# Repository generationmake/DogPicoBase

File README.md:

# DogPicoBase
Board with Electronic Assembly DOG graphic display for the Raspberry Pi Pico

## pin usage

### Raspberry Pi Pico connector CN1

| **Pin** | **Pin Name** | **Signal**    | **Description**                  |
|:-------:|:------------:|:-------------:|:--------------------------------:|
| 1       | GP0          | DIS_A0        | data/command for display         |
| 2       | GP1          | DIS_RESET     | reset for display                |
| 3       | GND          | GND           |                                  |
| 4       | GP2          |               |                                  |
| 5       | GP3          |               |                                  |
| 6       | GP4          |               |                                  |
| 7       | GP5          |               |                                  |
| 8       | GND          | GND           |                                  |
| 9       | GP6          | DIS_CLK       | clock for display on SPI0        |
| 10      | GP7          | DIS_SI        | data for display on SPI0         |
| 11      | GP8          |               |                                  |
| 12      | GP9          |               |                                  |
| 13      | GND          | GND           |                                  |
| 14      | GP10         |               |                                  |
| 15      | GP11         |               |                                  |
| 16      | GP12         | I2C0_SDA      | to connector CN3                 |
| 17      | GP13         | I2C0_SCL      | to connector CN3                 |
| 18      | GND          | GND           |                                  |
| 19      | GP14         | DIS_CS        | chip select for display          |
| 20      | GP15         |               |                                  |
| 21      | GP16         | UART0_TX      | to connector CN2                 |
| 22      | GP17         | UART0_RX      | to connector CN2                 |
| 23      | GND          | GND           |                                  |
| 24      | GP18         | I2C1_SDA      | to connector CN4                 |
| 25      | GP19         | I2C1_SCL      | to connector CN4                 |
| 26      | GP20         | DISPLAY_BL_3  | backlight channel 3              |
| 27      | GP21         | DISPLAY_BL_2  | backlight channel 2              |
| 28      | GND          | GND           |                                  |
| 29      | GP22         | DISPLAY_BL_1  | backlight channel 1              |
| 30      | RUN          | RESET         | Reset for Board                  |
| 31      | GP26         | KEYPAD_A0     | analog input for keys            |
| 32      | GP27         |               |                                  |
| 33      | GND          | GND           |                                  |
| 34      | GP28         |               |                                  |
| 35      | ADC_VREF     |               |                                  |
| 36      | 3V3 (OUT)    | 3V3-rail      | supply voltage for board         |
| 37      | 3V3_EN       |               |                                  |
| 38      | GND          | GND           |                                  |
| 39      | VSYS         |               |                                  |
| 40      | VBUS         | 5V-rail       | supply voltage for board         |

### Qwiic I2C connector CN3

compatible to Sparkfun Qwiic. JST SH 1mm 4-pin.

| **Pin** | **Signal**    | **Description**                  |
|:-------:|:-------------:|:--------------------------------:|
| 1       | GND           |                                  |
| 2       | VCC           |                                  |
| 3       | I2C0_SDA      |                                  |
| 4       | I2C0_SCL      |                                  |

### Qwiic I2C connector CN4

compatible to Sparkfun Qwiic. JST SH 1mm 4-pin.

| **Pin** | **Signal**    | **Description**                  |
|:-------:|:-------------:|:--------------------------------:|
| 1       | GND           |                                  |
| 2       | VCC           |                                  |
| 3       | I2C1_SDA      |                                  |
| 4       | I2C1_SCL      |                                  |

### serial connector CN2

JST SH 1mm 4-pin.

| **Pin** | **Signal**    | **Description**                  |
|:-------:|:-------------:|:--------------------------------:|
| 1       | GND           |                                  |
| 2       | VCC           |                                  |
| 3       | UART0_TX      |                                  |
| 4       | UART0_RX      |                                  |

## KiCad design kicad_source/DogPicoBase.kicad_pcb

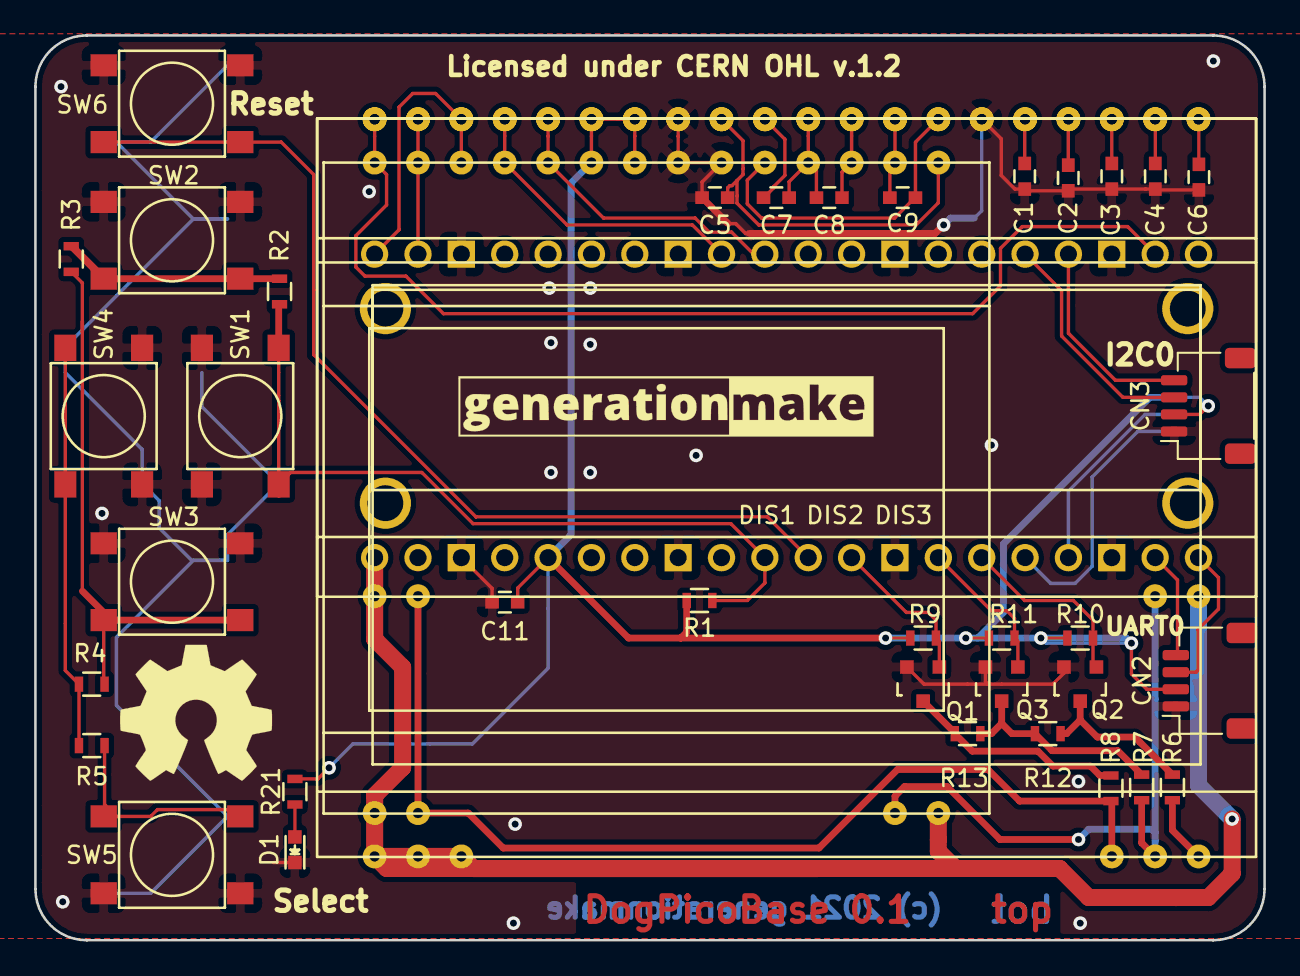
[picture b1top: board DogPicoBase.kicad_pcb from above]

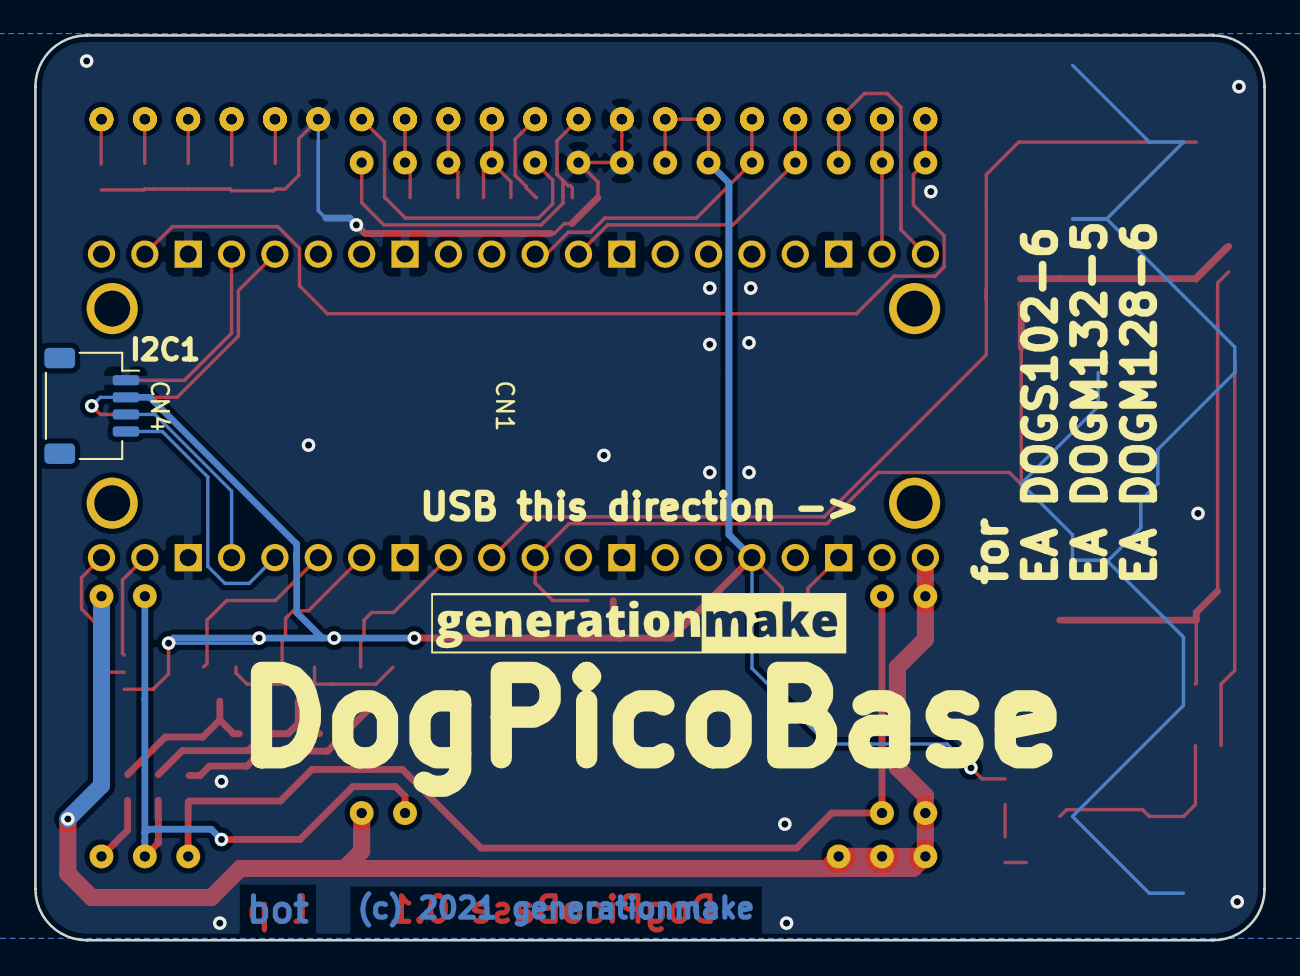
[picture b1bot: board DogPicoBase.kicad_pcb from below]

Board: 2 copper layers, 72.0 x 53.0 mm, 44 parts (3 on the bottom side), 41 nets.

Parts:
C1, C2, C3, C4, C5, C6, C7, C8, C9, C11: 1uF; C_0603
CN1: RASPBERRYPI_PICO; RASPI_PICO
CN2, CN3, CN4: SM04B-SRSS-TB; JST_SH_SM04B-SRSS-TB_1x04-1MP_P1.00mm_Horizontal
D1: 150060GS75000; LED_0603
DIS1: EA_DOGM128-6; EA_DOGM128
DIS2: EA_DOGM132-5; EA_DOGM081_162_163_132
DIS3: EA_DOGS102-6; EA_DOGS102
L1, L2: Label; generationmake_logo
L3: Label; OSHW-Symbol_8.9x8mm_SilkScreen
Q1, Q2, Q3: 2N7002; SOT-23
R1: 2k; R_0603
R2: 330; R_0603
R3: 620; R_0603
R4, R9, R10, R11, R21: 1k; R_0603
R5: 3k3; R_0603
R6, R7, R8: 30; R_0603
R12, R13: DNI; R_0603
SW1, SW2, SW3, SW4, SW5: TAST_VER; WE_430182080816
SW6: TAST_VER; WE_430182050816

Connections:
+3V3: C11.1, CN1.36, CN2.2, CN3.2, CN4.2, DIS1.34, DIS1.35, DIS2.34, DIS2.35, DIS3.22, DIS3.23, R1.1, R9.1, R10.1, R11.1, R21.2
+5V: CN1.40, DIS1.1, DIS1.2, DIS1.3, DIS2.1, DIS2.20, DIS3.1, DIS3.14
/BUTTON_DOWN: R3.2, R4.1, SW3.2, SW3.4
/BUTTON_LEFT: R4.2, R5.1, SW4.2, SW4.4
/BUTTON_SELECT: R5.2, SW5.2, SW5.4
/BUTTON_UP: R2.2, R3.1, SW2.2, SW2.4
/DISPLAY_BL_1: CN1.29, Q1.1, R9.2
/DISPLAY_BL_2: CN1.27, Q3.1, R11.2
/DISPLAY_BL_3: CN1.26, Q2.1, R10.2
/DIS_A0: CN1.1, DIS1.38, DIS2.38, DIS3.26
/DIS_C1: DIS1.18, DIS2.2, DIS3.2, R8.2
/DIS_C2: DIS1.19, DIS2.19, DIS3.13, R7.1
/DIS_C3: DIS1.20, R6.1
/DIS_CAP1N: C7.2, C8.1, DIS1.30, DIS2.30, DIS3.18
/DIS_CAP1P: C8.2, DIS1.29, DIS2.29, DIS3.17
/DIS_CAP2N: C9.2, DIS1.27, DIS2.27, DIS3.19
/DIS_CAP2P: C9.1, DIS1.28, DIS2.28, DIS3.16
/DIS_CAP3P: C7.1, DIS1.31, DIS2.31
/DIS_CLK: CN1.9, DIS1.37, DIS2.37, DIS3.25
/DIS_CS: CN1.19, DIS1.40, DIS2.40, DIS3.28
/DIS_RESET: CN1.2, DIS1.39, DIS2.39, DIS3.27
/DIS_SI: CN1.10, DIS1.36, DIS2.36, DIS3.24
/DIS_V0: C6.1, DIS1.21, DIS2.21
/DIS_V1: C4.1, DIS1.22, DIS2.22
/DIS_V2: C3.1, DIS1.23, DIS2.23
/DIS_V3: C2.1, DIS1.24, DIS2.24
/DIS_V4: C1.1, DIS1.25, DIS2.25
/DIS_VOUT: C5.1, DIS1.32, DIS2.32, DIS3.15
/I2C0_SCL: CN1.17, CN3.4
/I2C0_SDA: CN1.16, CN3.3
/I2C1_SCL: CN1.25, CN4.4
/I2C1_SDA: CN1.24, CN4.3
/KEYPAD_A0: CN1.31, R1.2, R2.1, SW1.2, SW1.4
/RESET: CN1.30, SW6.2, SW6.4
/UART0_RX: CN1.22, CN2.4
/UART0_TX: CN1.21, CN2.3
GND: C1.2, C2.2, C3.2, C4.2, C5.2, C6.2, C11.2, CN1.3, CN1.8, CN1.13, CN1.18, CN1.23, CN1.28, CN1.33, CN1.38, CN2.1, CN3.1, CN4.1, D1.1, DIS1.26, DIS1.33, DIS2.26, DIS2.33, DIS3.20, DIS3.21, Q1.2, Q2.2, Q3.2, SW1.1, SW1.3, SW2.1, SW2.3, SW3.1, SW3.3, SW4.1, SW4.3, SW5.1, SW5.3, SW6.1, SW6.3
unnamed: D1.2, R21.1
unnamed: Q1.3, R8.1, R13.1
unnamed: Q2.3, R6.2, R12.2
unnamed: Q3.3, R7.2, R12.1, R13.2

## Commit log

2021-02-15 added kicad project files
2021-02-15 added pico connector to schematic
2021-02-15 updated schematic
2021-02-16 added RGB backlight, updated layout
2021-09-02 added information on pin usage

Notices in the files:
kicad_source/DogPicoBase.kicad_pcb:
Licensed under CERN OHL v.1.2
(c) 2021 generationmake
This documentation describes Open Hardware and is licensed
under the CERN OHL v. 1.2.
of the CERN OHL v.1.2. (http://ohwr.org/cernohl). This documentation
